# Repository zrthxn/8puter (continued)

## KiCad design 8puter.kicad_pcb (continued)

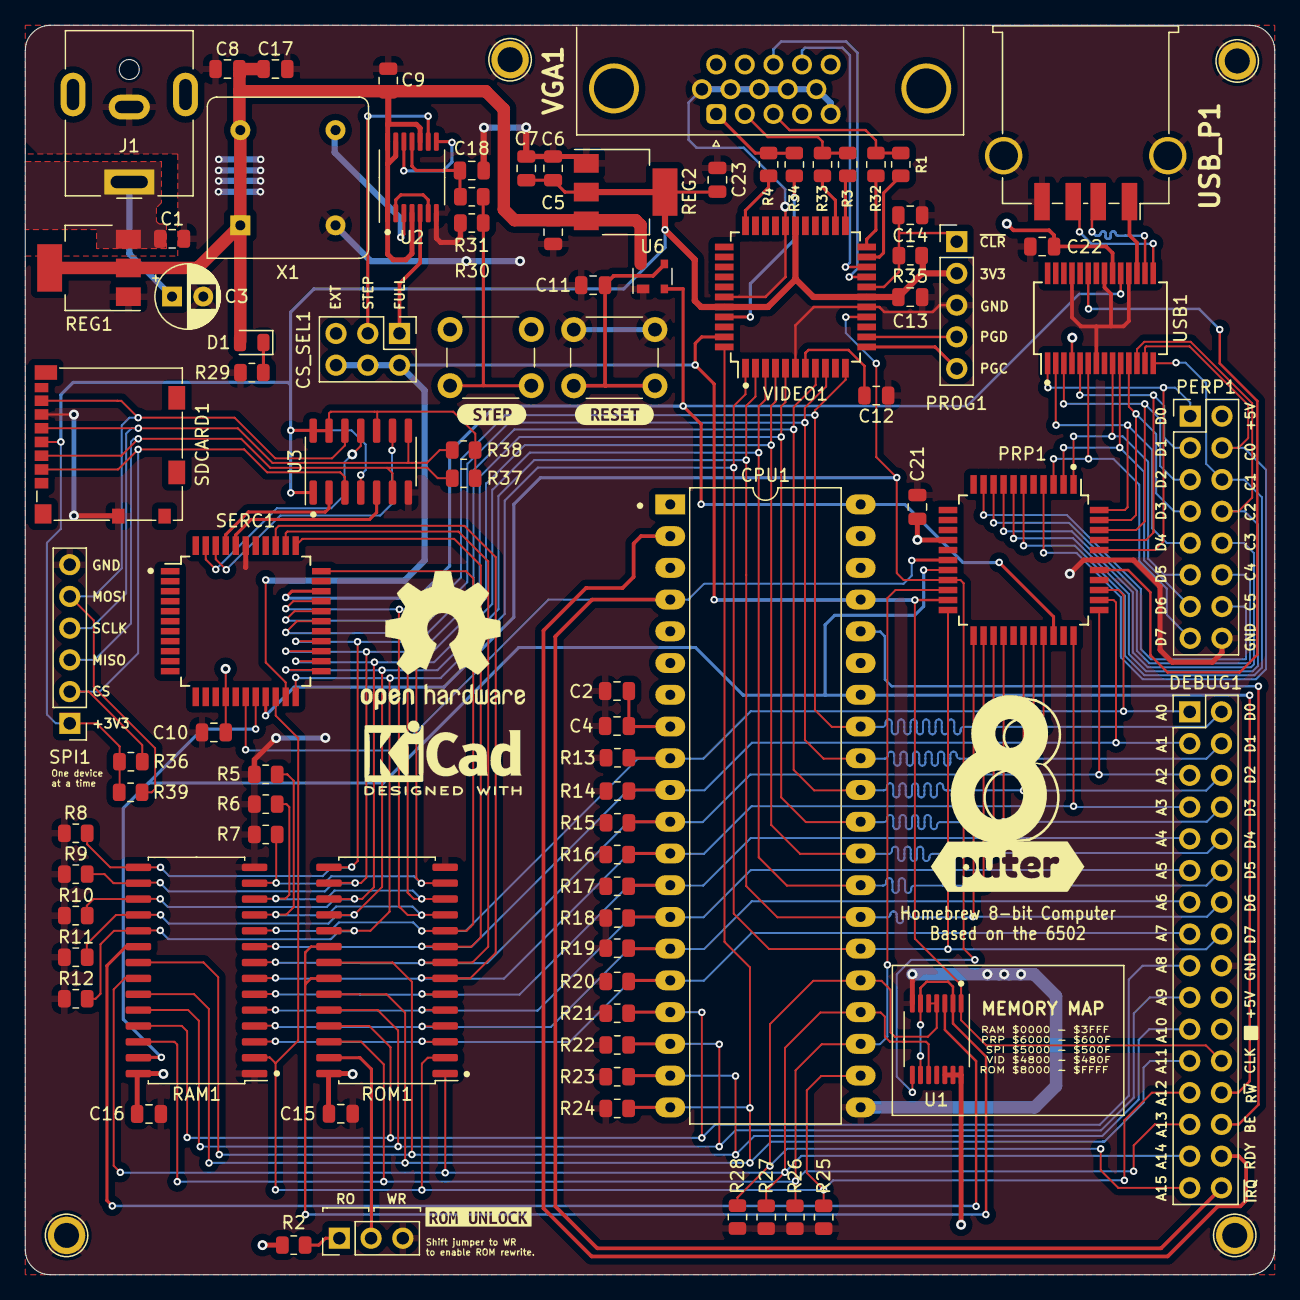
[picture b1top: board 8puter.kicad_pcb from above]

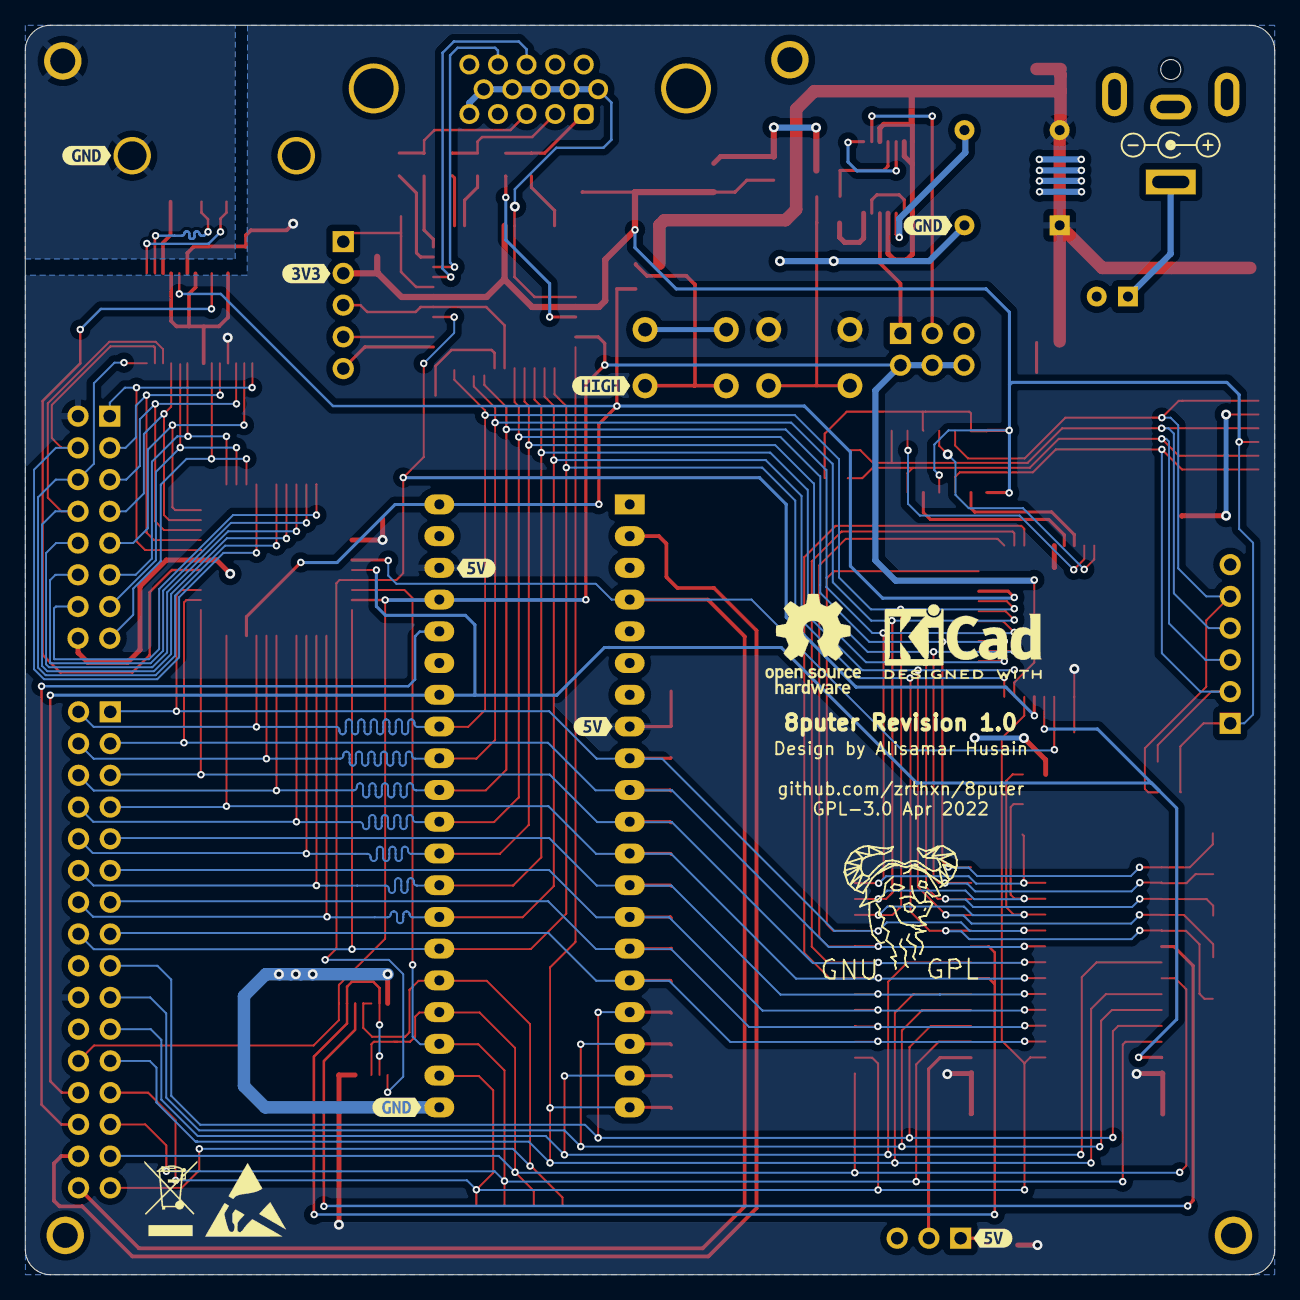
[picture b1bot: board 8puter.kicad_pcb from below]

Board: 2 copper layers, 100.0 x 100.0 mm, 99 parts (8 on the bottom side), 89 nets.

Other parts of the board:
kibuzzard-628B4C0E, kibuzzard-628B4C0E#2, kibuzzard-628B4C0E#3: G***; kibuzzard-628B4C0E
kibuzzard-628B4D67: G***; kibuzzard-628B4D67
kibuzzard-628B4DA2: G***; kibuzzard-628B4DA2
kibuzzard-628B4EC0: G***; kibuzzard-628B4EC0
kibuzzard-628B4F23: G***; kibuzzard-628B4F23
kibuzzard-628B4F43: G***; kibuzzard-628B4F43
kibuzzard-628B4F86, kibuzzard-628B4F86#2: G***; kibuzzard-628B4F86
kibuzzard-628B50D2: G***; kibuzzard-628B50D2
kibuzzard-628B5292: G***; kibuzzard-628B5292

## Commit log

2022-04-05 Memory Module
2022-04-05 Basic schematic
2022-04-07 Bus control
2022-04-09 New address decoder
2022-04-09 todo clock
2022-04-10 Board layout, addr bus
2022-04-11 More routing, USB iface
2022-04-14 Pivot to 6502
2022-04-19 Serial interface
2022-04-20 Serial, debug and prph headers
2022-04-20 Pulldowns, minor reroute
2022-04-20 pretty picture
2022-04-21 First completed routing
2022-04-21 Gerber Plots
2022-04-22 board improvements
2022-04-22 some docs
2022-04-23 update schematic
2022-04-24 serial rollback
2022-04-27 fix peripherals, add SPI
2022-04-27 Cleanup board
2022-04-27 Zipup gerbers
2022-04-29 Clearances
2022-04-29 Gerber format
2022-04-29 Picture
2022-04-29 Huge mistake CPU fp
2022-04-29 images, plots
2022-04-29 bigger header pins
2022-05-02 small updates
2022-05-02 update readme
    update readme
    update readme
2022-05-03 better file structure
2022-05-11 Comments in Sch
2022-05-22 nicer label
2022-05-23 improve routing
2022-05-23 improve schematic
2022-05-28 video source
2023-07-11 KiCad v7
2023-08-01 Updated gerbers zip
2023-08-20 Board Revision
